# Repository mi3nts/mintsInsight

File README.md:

# mintsInsight
INSIGHT – IoT Networked Sensing Instructional Guide for Hands-on Training

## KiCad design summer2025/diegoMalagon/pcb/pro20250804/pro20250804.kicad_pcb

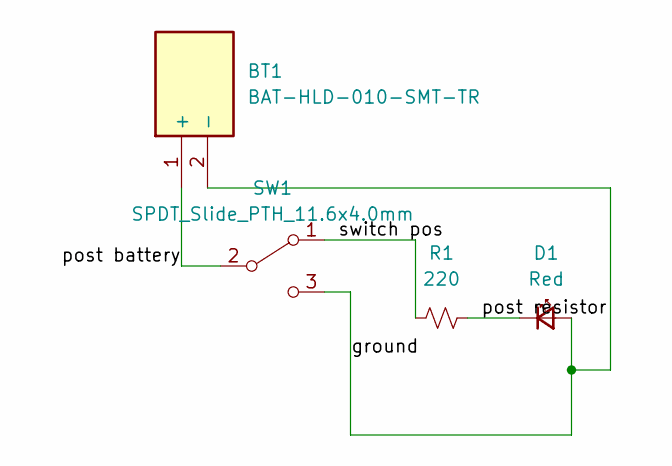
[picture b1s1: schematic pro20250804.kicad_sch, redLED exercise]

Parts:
BT1: BAT-HLD-010-SMT-TR; BatteryHolder_Keystone_1058_1x2032; Mouser Part Number 712-BAT-HLD-010SMTTR
D1: Red; LED_0402_1005Metric_Red
R1: 220; R_0603_1608Metric
SW1: SPDT_Slide_PTH_11.6x4.0mm; Slide_SPDT_PTH_11.6x4.0mm

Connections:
/ground: BT1.2 (-), D1.2 (A), SW1.3 (C)
/post battery: BT1.1 (+), SW1.2 (B)
/post resistor: D1.1 (K), R1.2
/switch pos: R1.1, SW1.1 (A)

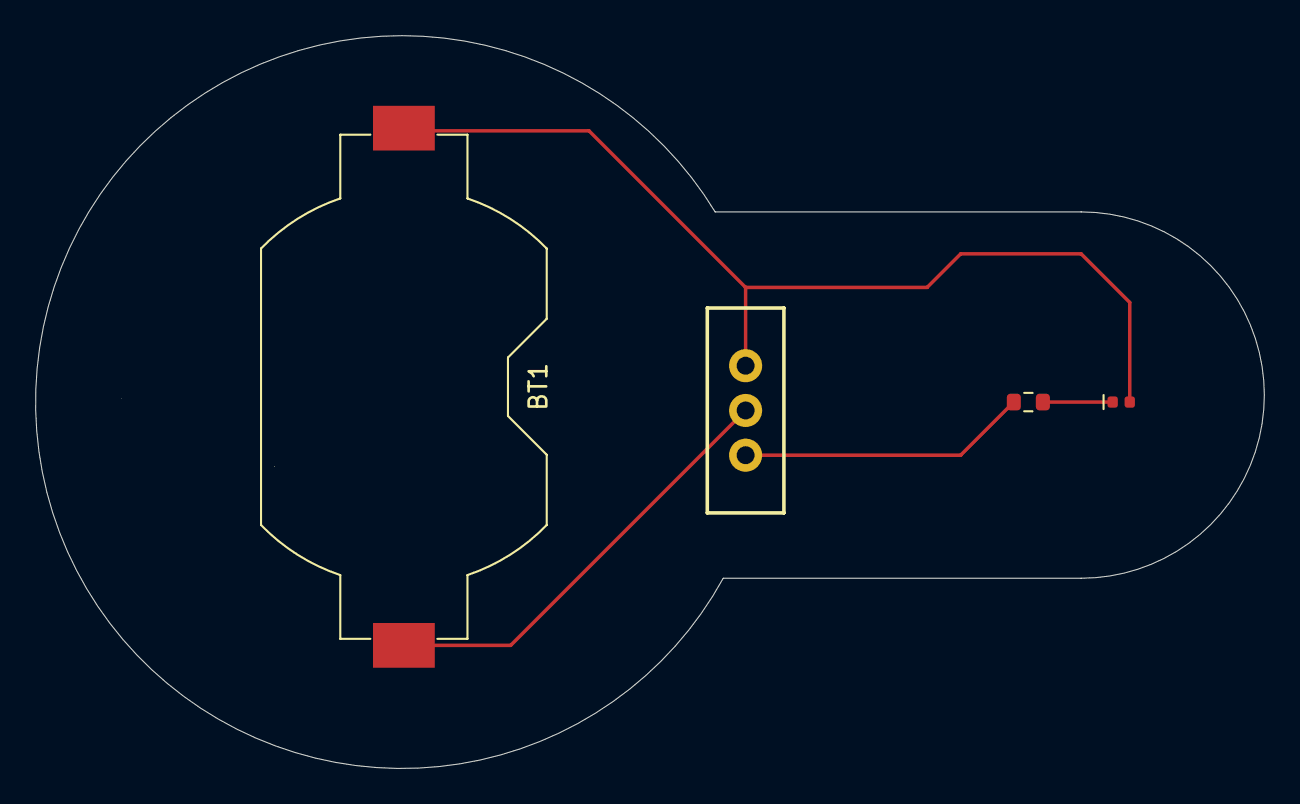
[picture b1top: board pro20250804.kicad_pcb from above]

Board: 2 copper layers, 69.8 x 41.6 mm, 4 parts (0 on the bottom side), 4 nets.

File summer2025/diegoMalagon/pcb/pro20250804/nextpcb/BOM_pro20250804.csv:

reference,value,footprint,MPN,manufacturer,Category,SKU,price,quantity
D1,Red,LED_0402_1005Metric_Red,SML-310LTT86,Rohm,LEDs,2500402653,0.13195,1
R1,220,R_0603_1608Metric,3-6318490-6,TE Connectivity (Tyco Electronics),Board to Board Connectors,2500419484,3.74111,1
S1,JS202011SCQN,Switch_Slide_JS202011SCQN,JS202011SCQN,C&K SYSTEMS,Universal,-,-,1

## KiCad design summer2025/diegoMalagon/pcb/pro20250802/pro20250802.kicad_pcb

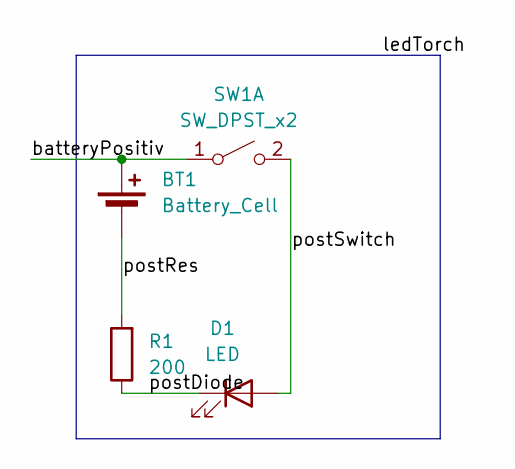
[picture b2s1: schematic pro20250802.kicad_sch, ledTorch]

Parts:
BT1: Battery_Cell; BatteryHolder_Keystone_1058_1x2032; MPN 1058
D1: LED; LED_5mm_Radial; MPN ltl1chkeknn
R1: 200; R_0201_0603Metric_Pad0.64x0.40mm_HandSolder; MPN CRCW02011K00FKED
SW1: SW_DPST_x2; SW_TH_Tactile_Omron_B3F-10xx; MPN B3F-1020

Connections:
/batteryPositiv: BT1.1 (+), SW1.1 (A)
/postDiode: D1.1 (K), R1.1
/postRes: BT1.2 (-), R1.2
/postSwitch: D1.2 (A), SW1.2 (B)

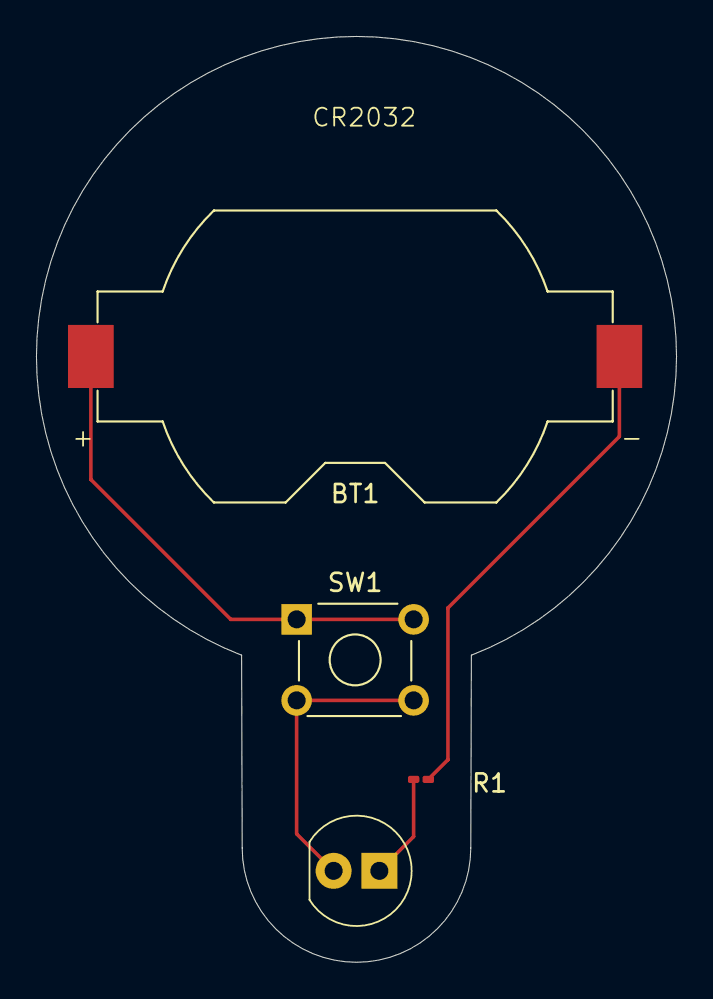
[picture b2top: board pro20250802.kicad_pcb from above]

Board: 2 copper layers, 35.6 x 51.4 mm, 4 parts (0 on the bottom side), 4 nets.

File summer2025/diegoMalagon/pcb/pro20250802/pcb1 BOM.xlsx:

Designator | Footprint | Quantity | Designation | Supplier and ref
D1 | LED_5mm_Radial | 1 | LED
SW1 | SW_TH_Tactile_Omron_B3F-10xx | 1 | SW_DPST_x2
BT1 | BatteryHolder_Keystone_1058_1x2032 | 1 | Battery_Cell
R1 | R_0201_0603Metric_Pad0.64x0.40mm_HandSolder | 1 | 200

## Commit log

2025-06-16 minor updates
2025-06-16 Added diagram for INA219 connection
2025-06-16 Added Battery_INA219.drawio
2025-06-16 volatic battery volatge sensing diagram
2025-06-16 created INA219 file
2025-06-16 Added INA219connectionDiagram.drawio.png
2025-06-16 updated file structure
2025-06-16 Added ina219DiagramXml.drawio
2025-06-16 Added ina219DiagramPng.drawio.png
2025-06-16 added INA219 file
2025-06-16 added initial ina219 firmware
2025-06-16 updatedina219 firmware
2025-06-16 updated ina219 firmware
2025-06-16 working INA219 driver (2nd not tested)
2025-06-16 working INA219 main for both sensors
2025-06-23 new file structure
2025-06-23 changed the library dependency
2025-06-23 changed file structure
2025-06-23 moved a file
2025-06-23 moved files
2025-06-23 changes made to INA219.py
2025-06-23 'added functions.py'
2025-06-23 'added csv export ability'
2025-06-23 modified INA219.py
2025-06-23 updated Datasheet
2025-06-23 created datasheets directory
2025-06-23 added file structure
2025-06-23 'moved files'
2025-06-23 'added file structure'
2025-06-23 'deleted redundant file'
2025-06-23 'added sensorDefinitions directory'
2025-06-23 'renamed directory'
2025-06-23 'added bme280 yaml file '
2025-06-23 upated ips7100 yaml
2025-06-23 updated yaml file with new definitions
2025-06-23 added RG15 and yaml files
2025-06-23 ' added rg15 yaml file'
2025-06-23 modified yaml files and added new sensor def
2025-06-25 'added readme.md file'
2025-06-25 'edited md file'
2025-06-25 Add files via upload
    circuit diagram for project of the week of June 23
2025-06-25 'edited readMe md file'
2025-06-25 'edited markdown file'
2025-06-26 Co2 sensor
2025-06-30 'updated function.py'
2025-06-30 'updated markdown file'
2025-06-30 'added a markdown file'
2025-07-02 initial cozir firmware test
2025-07-02 assertionError bug fix?
2025-07-02 another bug fix attempt; maybe fixes sensor crashing
2025-07-02 added cozir.py credit
2025-07-02 'added IPS7100 I2C driver'
2025-07-02 'added main file to run IPS7100 driver'
2025-07-02 'edited'
2025-07-02 Add files via upload
    This works well.
2025-07-02 'transferred debugged driver from testing repo'
2025-07-08 added co2 deque and basic csvWriter file
2025-07-08 updated main to account for filter and unfiltered
2025-07-08 search unfiltered co2 until found
2025-07-08 more clarity in main.py
2025-08-18 'added grafan folder with windrose stuff'
2025-09-04 Added Diagram.drawio
2025-09-11 renke sensor to usb converter
2025-09-11 Rename Untitled Diagram.jpg to renkeToUSB.jpg
2025-09-11 Added renkeToUSB.drawio.png
2025-09-18 Added OPCN3wiringDiagram.drawio.png
2025-09-18 'Initial commit of lung diagram and windrose script'
2025-09-18 'added opcDriver.py'
2025-09-18 added opc driver
2025-09-18 'added opcTestRead.py and modified opcDriver.py for new read functionality'
2025-09-18 'edited files'
2025-09-18 'fixed typo in opcDriver.py and added cleanup function'
2025-09-18 'fixed typo in opcDriver.py and opcTestRead.py'
2025-09-18 'removed unnecessary print statements from opcDriver and opcTestRead'
2025-09-18 'changed struct.unpack to read single float instead of three floats'
2025-09-18 'trying a different opcTestRead.py'
2025-09-18 'new opcDriver and opcTestRead files'
2025-09-18 'fixed mistake in opcDriver.py'
2025-09-25 'Initial commit of opcN2InterfacingInfo.md'
2025-09-25 updated driver to match the SPI commands on the OPC N2 datasheet.
2025-09-25 'fixed typo in opcDriver.py'
2025-09-25 'added a sleep to allow device to stabilize'
2025-09-25 'edited test for debugging'
2025-09-25 'changed test for debugging'
2025-09-25 'changed print output for debugging and added small delay in spiTransfer to improve reliability'
2025-09-25 'debugging'
2025-09-25 'edited Transfer helper '
2025-09-25 'debuggging'
2025-09-25 'debug: add frame validation to opcDriver.py'
2025-09-25 'added validation for opcRead() to ensure data is received before processing'
2025-09-25 'changed testread'
2025-09-25 'added opcRaw function for raw command response with mode and logging to csv'
2025-09-25 'changed csv file name'
2025-09-25 'changed opcTestRead.py and opcDriver.py to add opcRaw function and use it in opcTestRead.py'
2025-09-25 added serial print
2025-09-25 'edited transfer functions to include stabilization delay and raw read capability'
2025-09-25 'initial commit of opcLogger.py with filtered logging to CSV'
2025-09-25 'incorporated logger'
2025-09-25 'edited file name'
2025-10-02 'added PCB directory '
2025-10-02 Updated PCB
2025-10-07 'added new pcb'
